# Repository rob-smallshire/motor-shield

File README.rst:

motor-shield
============

Arduino SN754410 Quad Half-H motor driver shield.

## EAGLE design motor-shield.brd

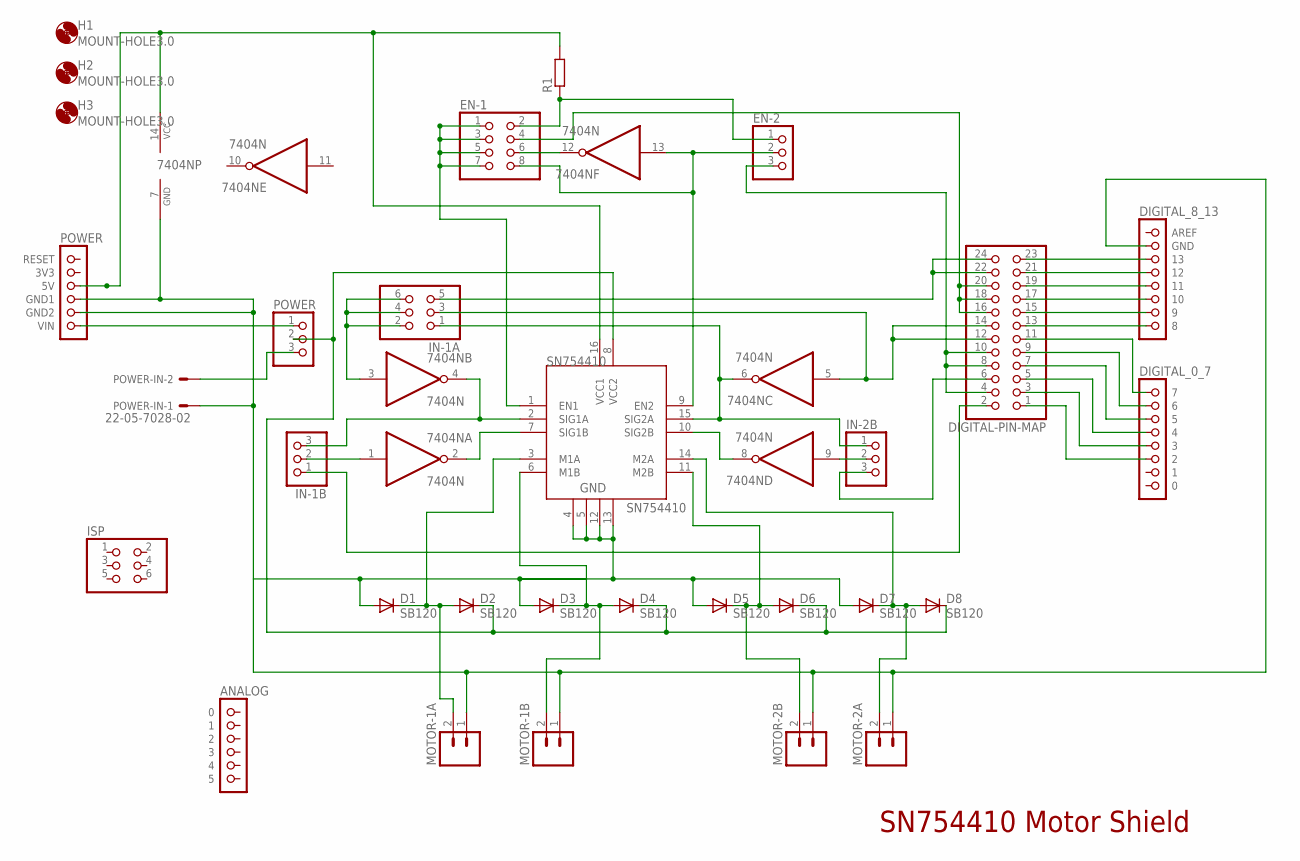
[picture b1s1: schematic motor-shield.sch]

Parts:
7404N: 7404N; DIL14
D1, D2, D3, D4, D5, D6, D7, D8: SB120; DO41-10
DIGITAL-PIN-MAP: PINHD-2X12; 2X12
EN-1: PINHD-2X4; 2X04
EN-2: PINHD-1X3; 1X03
H1, H2, H3: MOUNT-HOLE3.0; 3,0
IN-1A: PINHD-2X3; 2X03
IN-1B, IN-2B: PINHD-1X3; 1X03
ISP: PINHD-2X3; 2X03
MOTOR-1A, MOTOR-1B, MOTOR-2A, MOTOR-2B: M023.5MM-NO_SILK; SCREWTERMINAL-3.5MM-2-NS
POWER: PINHD-1X3; 1X03
POWER-IN: 22-05-7028-02; 7395-02
R1: R-EU_0207/10; 0207/10
SN754410: SN754410; DIP16
U$1: POWER; 1X06
U$2: ANALOG; 1X06
U$3: DIGITAL_0_7; 1X08
U$4: DIGITAL_8_13; 1X08

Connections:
5V: 7404N.14 (VCC), R1.2, SN754410.16 (VCC1), U$1.3 (5V)
GND: 7404N.7 (GND), D1.A, D3.A, D5.A, D7.A, MOTOR-1A.1, MOTOR-1B.1, MOTOR-2A.1, MOTOR-2B.1, POWER-IN.1, SN754410.4, SN754410.5, SN754410.12, SN754410.13, U$1.4 (GND1), U$1.5 (GND2), U$4.2 (GND)
unnamed: 7404N.4 (O), IN-1B.3, SN754410.2 (SIG1A)
unnamed: 7404N.2 (O), SN754410.7 (SIG1B)
unnamed: 7404N.6 (O), IN-1A.1, IN-2B.1, SN754410.15 (SIG2A)
unnamed: 7404N.8 (O), SN754410.10 (SIG2B)
unnamed: 7404N.9 (I), IN-2B.2
unnamed: 7404N.1 (I), IN-1B.2
unnamed: 7404N.12 (O), EN-1.6
unnamed: DIGITAL-PIN-MAP.23, U$4.3 (13)
unnamed: EN-1.2, EN-2.1, R1.1
unnamed: 7404N.13 (I), EN-1.8, EN-2.2, SN754410.9 (EN2)
unnamed: 7404N.5 (I), DIGITAL-PIN-MAP.12, DIGITAL-PIN-MAP.14, IN-1A.3
unnamed: EN-1.1, EN-1.3, EN-1.5, EN-1.7, SN754410.1 (EN1)
unnamed: DIGITAL-PIN-MAP.16, DIGITAL-PIN-MAP.18, DIGITAL-PIN-MAP.20, EN-1.4
unnamed: DIGITAL-PIN-MAP.4, DIGITAL-PIN-MAP.8, DIGITAL-PIN-MAP.10, EN-2.3
unnamed: 7404N.3 (I), IN-1A.2, IN-1A.4, IN-1A.6
unnamed: DIGITAL-PIN-MAP.6, IN-2B.3
unnamed: DIGITAL-PIN-MAP.2, IN-1B.1
unnamed: DIGITAL-PIN-MAP.22, DIGITAL-PIN-MAP.24, IN-1A.5
unnamed: DIGITAL-PIN-MAP.21, U$4.4 (12)
unnamed: DIGITAL-PIN-MAP.19, U$4.5 (11)
unnamed: DIGITAL-PIN-MAP.17, U$4.6 (10)
unnamed: DIGITAL-PIN-MAP.15, U$4.7 (9)
unnamed: DIGITAL-PIN-MAP.13, U$4.8
unnamed: POWER.1, U$1.6 (VIN)
unnamed: DIGITAL-PIN-MAP.11, U$3.1 (7)
unnamed: DIGITAL-PIN-MAP.9, U$3.2 (6)
unnamed: DIGITAL-PIN-MAP.7, U$3.3 (5)
unnamed: DIGITAL-PIN-MAP.5, U$3.4
unnamed: DIGITAL-PIN-MAP.3, U$3.5 (3)
unnamed: DIGITAL-PIN-MAP.1, U$3.6 (2)
unnamed: D1.C, D2.A, MOTOR-1A.2, SN754410.3 (M1A)
unnamed: D3.C, D4.A, MOTOR-1B.2, SN754410.6 (M1B)
unnamed: D5.C, D6.A, MOTOR-2B.2, SN754410.11 (M2B)
unnamed: D7.C, D8.A, MOTOR-2A.2, SN754410.14 (M2A)
V-MOTOR: D2.C, D4.C, D6.C, D8.C, POWER.2, SN754410.8 (VCC2)
VEXT: POWER.3, POWER-IN.2

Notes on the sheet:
SN754410 Motor Shield

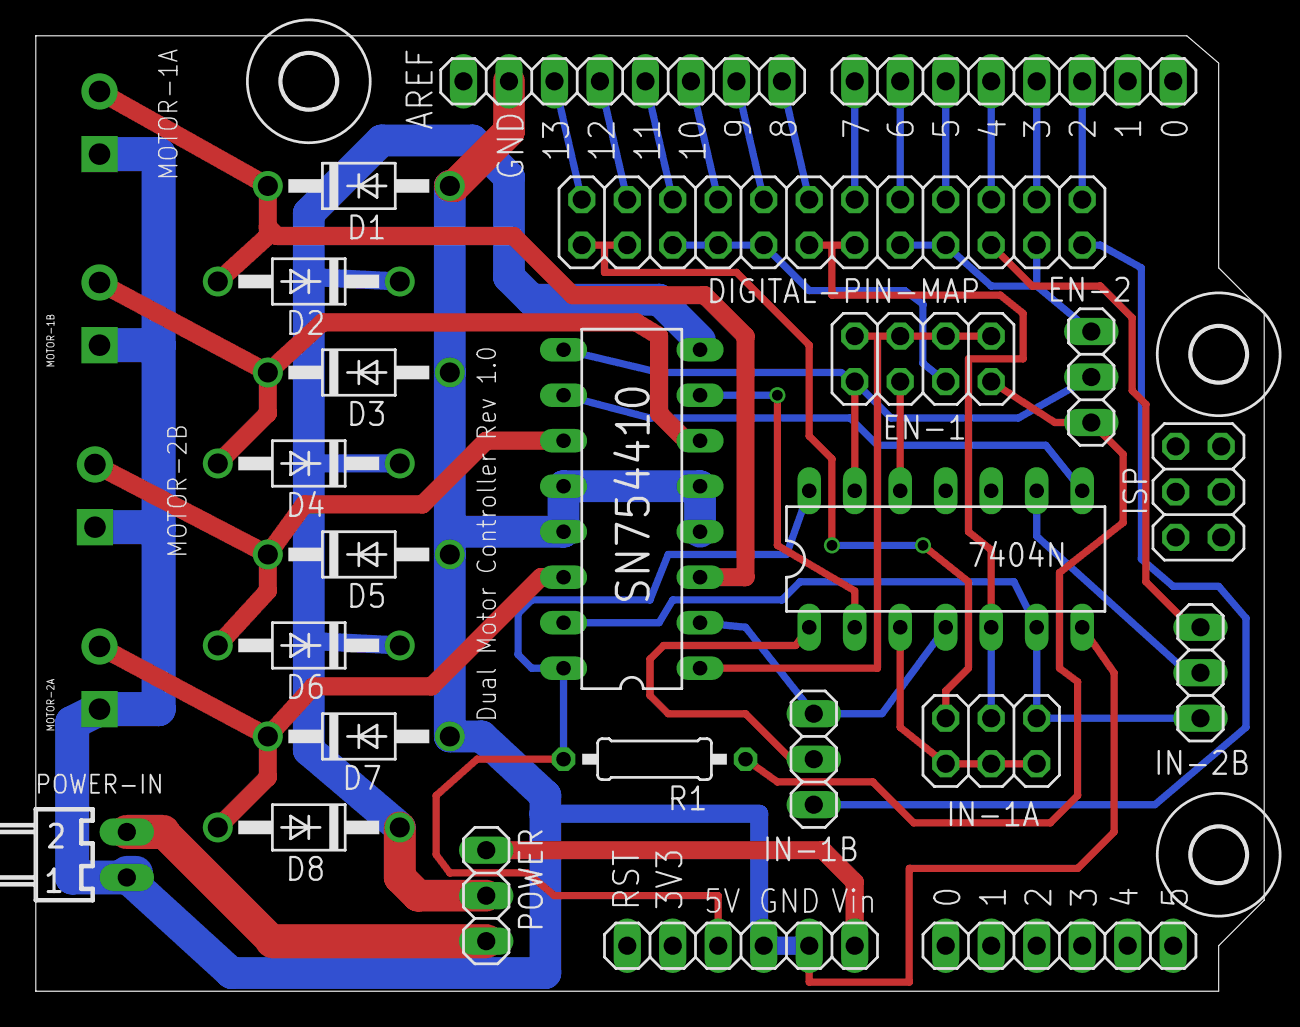
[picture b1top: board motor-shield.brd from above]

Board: 2 copper layers, 68.6 x 53.3 mm, 31 parts (0 on the bottom side), 38 nets.

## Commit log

2013-05-17 Rename README.md to README.rst
2013-05-17 Original import from canisp
2013-05-17 EAGLE Description file
